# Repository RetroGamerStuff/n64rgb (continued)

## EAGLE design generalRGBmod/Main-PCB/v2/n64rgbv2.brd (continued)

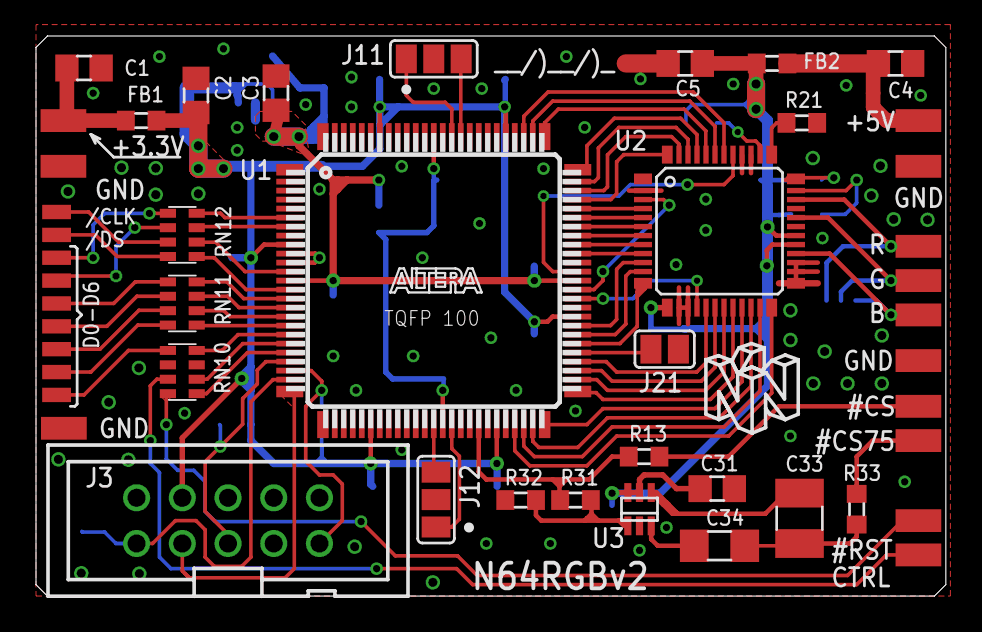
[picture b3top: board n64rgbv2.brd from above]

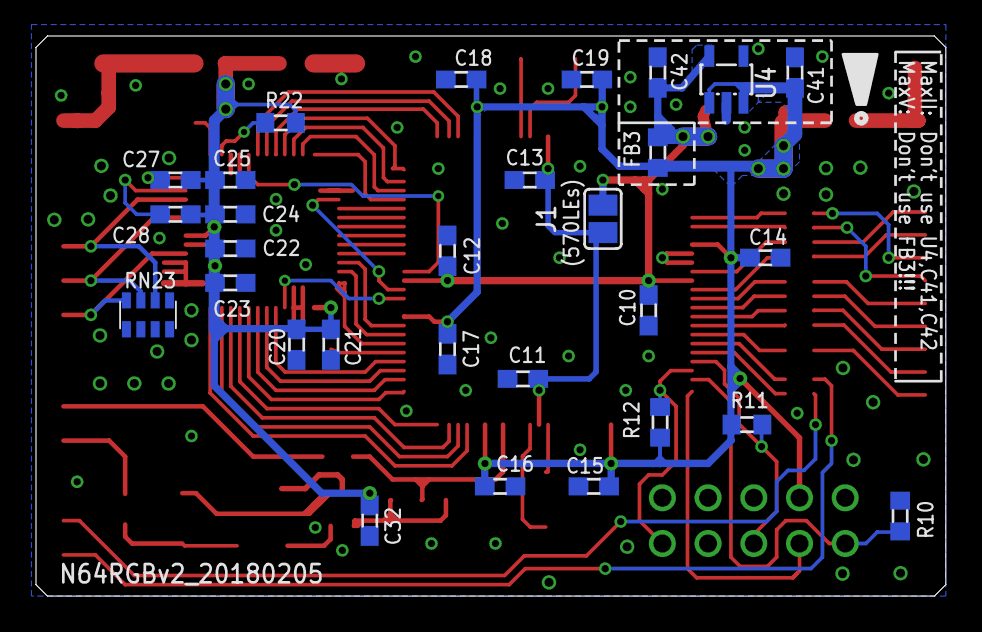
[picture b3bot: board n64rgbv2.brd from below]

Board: 2 copper layers, 50.5 x 31.1 mm, 76 parts (29 on the bottom side), 79 nets.

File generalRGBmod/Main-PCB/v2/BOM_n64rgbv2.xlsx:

Designator | MPN | QTY | DESCRIPTION | VALUE | PACKAGE | NOTES
ICs and Regulators
U1 | 5M570ZT100C4N | 1 | CPLD with 570LEs |  | TQFP100 | Close J1
 | 5M240ZT100C4N |  | CPLD with 240LEs |  | TQFP100 | Alternative to 5M570ZT100 with less LEs, leave J1 open
U2 | ADV7125KSTZ50 | 1 | Video DAC 8bit, 3Ch. |  | 48-LQFP | can be replaced with ADV7123KSTZ50 on demand
U3 | TSH122ICT | 1 | Video buffer |  | SC-70-6
U4 | TLV70018DDCR | 1 | 1.8V LDO regulator |  | SOT-23-5
Power Supply Filtering
C1,C4 | GRM31CR61A476ME15L | 2 | Ceramic capacitor, X5R | 47uF / 6.3V | SMD0805
FB1,FB2 | BLM18PG471SN1D | 2 | Ferrit bead |  | SMD0603
Remaining passive components
C2,C3,C5,C31 | GRM219R60J476ME44D | 4 | Ceramic capacitor, X5R | 10uF / 6.3V | SMD0805
C10-C19,C20,C22,C24,C27,C28 | GRM188R71H104KA93J | 15 | Ceramic capacitor, X7R | 0.1uF / 50V (10%) | SMD0603
C21,C23,C25,C32 | GRM188R70J103KA01D | 4 | Ceramic capacitor, X7R | 0.01uF / 50V | SMD0603
C33 | GRM32DR60J336ME19L | 1 | Ceramic capacitor, X5R | 33uF / 6.3V | SMD1210
C34 | GRM31CR60J226KE19L | 1 | Ceramic capacitor, X5R | 22uF / 6.3V | SMD1206
C41,C42 | GRM18R60J105KA01J | 2 | Ceramic capacitor, X5R | 1uF / 6.3V | SMD0603
R10 | CRCW06031K00FKTB | 1 | Resistor | 1kohm (1%) | SMD0603
R11, R12 | CRCW0603-10K | 2 | Resistor | 10kohm (1%) | SMD0603
R13 | RC0603FR-07330RL | 1 | Resistor | 330ohm (1%) | SMD0603
R21 | RC0603FR-07523RL | 1 | Resistor | 518 | SMD0603 | with ADV7123: use 516ohm resistor; for PAL-Standard: 528ohm/527ohm
R22,R31 | RC0603FR-074K7L | 2 | Resistor | 4.7kohm (1%) | SMD0603
R32 | RC0603FR-07475RL | 1 | Resistor | 475ohm (1%) | SMD0603
R33 | RC0603FR-0775RL | 1 | Resistor | 75 | SMD0603
RN10,RN11,RN12 | CAT16-47R0F4LF / CAY16-47R0F4LF | 3 | Resistor Array (4x) | 47 | SMD1206 | Only use this if you don't have resistors at the RCP output
 | BK32164M121-T |  | Ferrite Beads MULTILYR CHP | BD 120OHMS 25% | SMD1206 | Use this if you have resistors at the RCP output
RN23 | CAT16-75R0F4LF / CAY16-75R0F4LF | 1 | Resistor Array (4x) | 75 | SMD1206
J3 | 30310-6002HB | 1 |  |  |  | JTAG Connector
Unpopulated Footprints
FB3 | Don't use FB3 in MaxV setup!!! Otherwise you'll harm your CPLD at first power c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
MPNs are only suggestions! You can use equivalent components, too.

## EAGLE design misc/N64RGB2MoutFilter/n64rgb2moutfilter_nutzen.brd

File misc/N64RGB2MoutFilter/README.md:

### Jumper

#### SJ1

Sync source at MultiOut
 - SJ1.1 closed: forward sync to pin 7 of the MultiOut
 - SJ1.2 closed: forward sync to pin 3 of the MultiOut
 - you are allowed to close both sides of this jumper

#### SJ2

flex assembly setup (see [BOM sheet](./doc/N64RGB2MoutFilter_BOM.xlsx)
 - close all three jumper if you do not use the filter assembly

#### SJ3

Sync source at the modding board
 - J3.1: Use TTL C-Sync
 - J3.2: Use 75ohm Sync
 - Never use both!

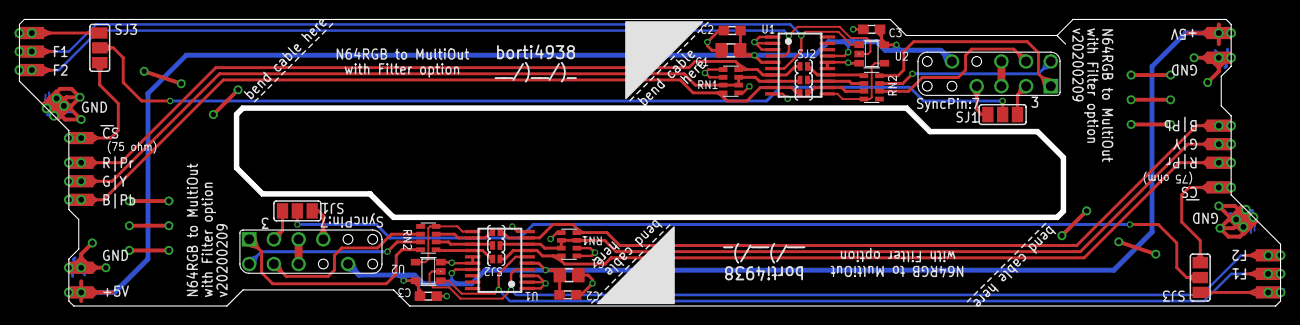
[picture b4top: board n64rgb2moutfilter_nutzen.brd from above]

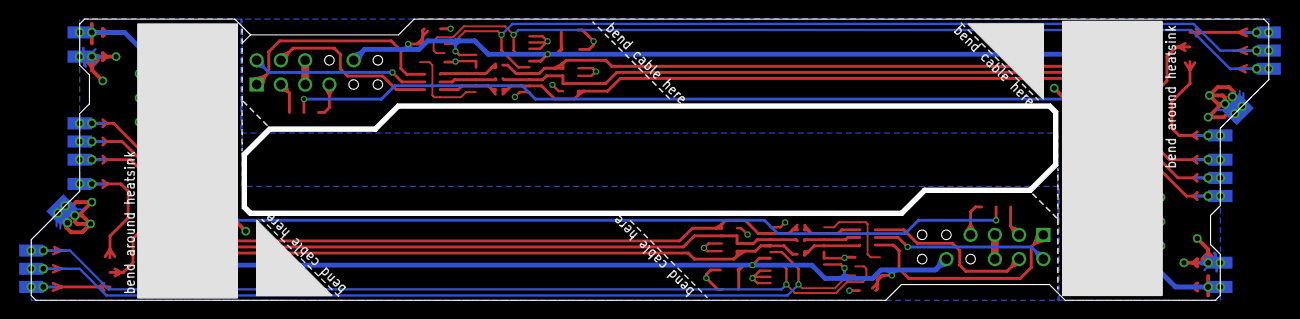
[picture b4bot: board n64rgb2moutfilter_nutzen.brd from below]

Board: 2 copper layers, 129.7 x 29.5 mm, 70 parts (22 on the bottom side), 38 nets.

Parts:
B/PB, B/PB1, B/PB2, B/PB3: SMD1,27-2,54
C1, C4: 22u; C0805
C2, C3, C5, C6: 0.1u; C0603
CS75#, CS75#1, CS75#2, CS75#3: SMD1,27-2,54
CS#, CS#1, CS#2, CS#3: SMD1,27-2,54
E$1, E$2: SNES_MULTIAV_RGBSY
F1, F2, F3, F4, F5, F6, F7, F8: SMD1,27-2,54
G/Y, G/Y1, G/Y2, G/Y3: SMD1,27-2,54
P_GND1, P_GND2, P_GND3, P_GND4, P_GND5, P_GND6, P_GND7, P_GND8, P_GND9, P_GND10, P_GND11, P_GND12: SMD1,27-2,54
P_VCC_5V, P_VCC_5V1, P_VCC_5V2, P_VCC_5V3: SMD1,27-2,54
R/PR, R/PR1, R/PR2, R/PR3: SMD1,27-2,54
RN1, RN2, RN3, RN4: 75; CTS742C083
SJ1, SJ2, SJ3, SJ4: SJ_2
SJ2B, SJ2B1, SJ2G, SJ2G1, SJ2R, SJ2R1: SJ_SMALL
U1, U3: THS7368
U2, U4: SOT23-5

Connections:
5V: C1.2, C2.1, C3.1, E$1.10, P_VCC_5V.1, P_VCC_5V1.1, U1.5, U1.17, U2.5
5V1: C4.2, C5.1, C6.1, E$2.10, P_VCC_5V2.1, P_VCC_5V3.1, U3.5, U3.17, U4.5
#CS: E$1.3, SJ1.1
#CS1: E$2.3, SJ2.1
#CS.75.I: CS75#.1, CS75#1.1, SJ3.3
#CS.75.I1: CS75#2.1, CS75#3.1, SJ4.3
#CS.I: CS#.1, CS#1.1, SJ3.1
#CS.I1: CS#2.1, CS#3.1, SJ4.1
#CS.SEL: SJ1.2, SJ3.2
#CS.SEL1: SJ2.2, SJ4.2
BLUE: B/PB.1, B/PB1.1, RN1.8, SJ2R.1, U1.9
BLUE1: B/PB2.1, B/PB3.1, RN3.8, SJ2R1.1, U3.9
BLUE.OUT: RN2.3, SJ2R.2, U1.12
BLUE.OUT1: RN4.3, SJ2R1.2, U3.12
BLUE.OUT.1: E$2.4, RN4.6
BLUE.OUT.75: E$1.4, RN2.6
BYPASS_SF: RN2.4, U1.11, U2.4
BYPASS_SF1: RN4.4, U3.11, U4.4
F1: F1.1, F4.1, U1.6, U2.1
F2: F2.1, F3.1, U1.4, U2.2
F3: F5.1, F8.1, U3.6, U4.1
F4: F6.1, F7.1, U3.4, U4.2
GND: C1.1, C2.2, C3.2, E$1.5, E$1.6, P_GND1.1, P_GND2.1, P_GND3.1, P_GND4.1, P_GND5.1, P_GND6.1, RN1.1, RN1.5, RN1.6, U1.1, U1.2, U1.3, U1.10, U1.15, U1.16, U2.3
GND1: C4.1, C5.2, C6.2, E$2.5, E$2.6, P_GND7.1, P_GND8.1, P_GND9.1, P_GND10.1, P_GND11.1, P_GND12.1, RN3.1, RN3.5, RN3.6, U3.1, U3.2, U3.3, U3.10, U3.15, U3.16, U4.3
GREEN: G/Y.1, G/Y1.1, RN1.2, RN1.3, RN1.7, SJ2G.1, U1.8
GREEN1: G/Y2.1, G/Y3.1, RN3.2, RN3.3, RN3.7, SJ2G1.1, U3.8
GREEN.OUT: RN2.2, SJ2G.2, U1.13
GREEN.OUT1: RN4.2, SJ2G1.2, U3.13
GREEN.OUT.1: E$2.2, RN4.7
GREEN.OUT.75: E$1.2, RN2.7
LUMA: E$1.7, SJ1.3
LUMA1: E$2.7, SJ2.3
RED: R/PR.1, R/PR1.1, RN1.4, SJ2B.1, U1.7
RED1: R/PR2.1, R/PR3.1, RN3.4, SJ2B1.1, U3.7
RED1.OUT: RN2.1, SJ2B.2, U1.14
RED1.OUT1: RN4.1, SJ2B1.2, U3.14
RED.OUT.1: E$2.1, RN4.8
RED.OUT.75: E$1.1, RN2.8

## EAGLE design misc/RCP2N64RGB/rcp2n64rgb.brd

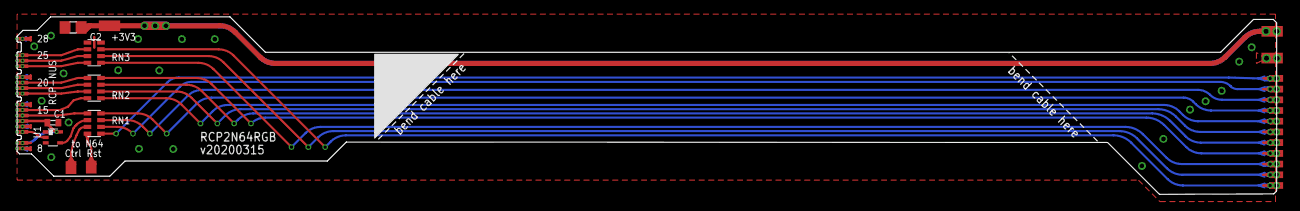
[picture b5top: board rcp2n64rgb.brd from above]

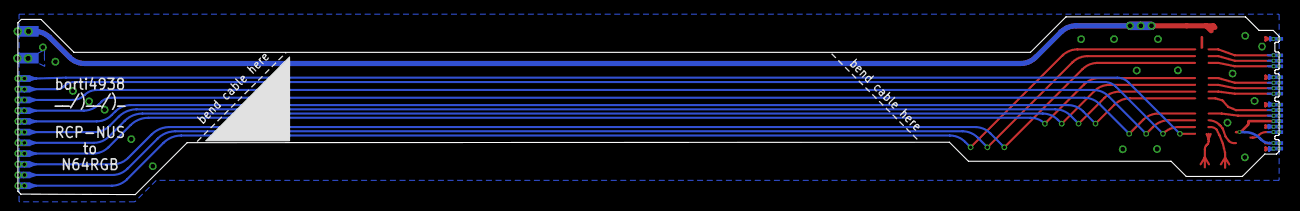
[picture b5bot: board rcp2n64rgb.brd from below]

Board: 2 copper layers, 149.4 x 21.1 mm, 67 parts (29 on the bottom side), 26 nets.

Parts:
/RST_A, /RST_A1: SMD0,8-1,6
C1: C0402
C2: 22u; C0805
CLOCK#, CLOCK#1: SMD0,8-1,6
CTRL_A, CTRL_A1: SMD0,8-1,6
D0, D1, D2, D3, D4, D5, D6, D7, D8, D9, D10, D11, D12, D13: SMD0,8-1,6
DSYNC#, DSYNC#1: SMD0,8-1,6
E$1, E$3, E$4, E$5, E$8, E$9, E$10, E$11, E$12, E$13, E$14, E$15, E$16, E$17, E$18, E$19, E$22, E$23, E$24, E$25, E$26, E$27, E$28, E$29, E$30, E$31, E$32, E$33, E$43, E$46, E$47: SMD0,45-1,35
E$2, E$6: SMD0.8SQ
GND: SMD0,45-1,35
P_GND0, P_GND1: SMD1,27-2,54
P_VCC_3V, P_VCC_3V1, P_VCC_3V3: SMD1,27-2,54
RN1, RN2, RN3: CTS742C083
U1: DCK_R-PDSO-G5

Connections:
3V3: C2.1, P_VCC_3V.1, P_VCC_3V1.1, P_VCC_3V3.1
#DSYNC: E$10.P$1, E$31.P$1, RN1.1
#DSYNC.1: DSYNC#.P$1, DSYNC#1.P$1, RN1.8
CTRL: E$2.P$1, RN1.3
CTRL.1: CTRL_A.P$1, CTRL_A1.P$1, RN1.6
D0: E$19.P$1, E$22.P$1, RN3.2
D0.1: D0.P$1, D7.P$1, RN3.7
D1: E$18.P$1, E$23.P$1, RN3.3
D1.1: D1.P$1, D8.P$1, RN3.6
D2: E$17.P$1, E$24.P$1, RN3.4
D2.1: D2.P$1, D9.P$1, RN3.5
D3: E$15.P$1, E$26.P$1, RN2.1
D3.1: D3.P$1, D10.P$1, RN2.8
D4: E$14.P$1, E$27.P$1, RN2.2
D4.1: D4.P$1, D11.P$1, RN2.7
D5: E$13.P$1, E$28.P$1, RN2.3
D5.1: D5.P$1, D12.P$1, RN2.6
D6: E$11.P$1, E$30.P$1, RN2.4
D6.1: D6.P$1, D13.P$1, RN2.5
GND: C1.2, C2.2, E$9.P$1, E$12.P$1, E$16.P$1, E$25.P$1, E$29.P$1, E$32.P$1, E$43.P$1, E$46.P$1, GND.P$1, P_GND0.1, P_GND1.1, RN3.1, RN3.8, U1.3
RST: E$6.P$1, RN1.4
RST.1: /RST_A.P$1, /RST_A1.P$1, RN1.5
VCC: C1.1, E$1.P$1, E$3.P$1, E$4.P$1, E$5.P$1, U1.5
VCLK: E$8.P$1, E$33.P$1, U1.2
VCLK.1: CLOCK#.P$1, CLOCK#1.P$1, RN1.7
VCLK_BUF: RN1.2, U1.4

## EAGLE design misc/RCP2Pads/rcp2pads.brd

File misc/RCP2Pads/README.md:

# A small Flex-PCB
## N64 RCP-NUS breakout

## Purpose

This PCB enables you to apply appropriate buffering to the RCP output pins for N64RGB installs. This is useful for any CPLD and FPGA RGB Kit like viletims N64RGB (public and commercial), N64RGBv2.1, N64Advanced and many more variations spreaded over the internet.

## Where to Order?

This board can be ordered from every service you want to choose, e.g. PCBWay.  
An easy small prototype solution though might be the flex cable service by [OSHPark](https://oshpark.com/).
Make sure to tick the flex service before going to the checkout when chosing for OSHPark!

## Pinout

From top to bottom (RCP on left, connector right)

| **Pin** | **Signal** |
|:-------:|:-----------|
| 13 | GND |
| 12 | D0 |
| 11 | D1 |
| 10 | D2 |
| 9 | D3 |
| 8 | D4 |
| 7 | D5 |
| 6 | D6 |
| 5 | #DSYNC |
| 4 | VCLK |
| 3 | GND |
| 2 | Ctrl. (controller port pin 2, pin 16 PIF-NUS) |
| 1 | Rst (pin 27 PIF-NUS) |

## Preparation

You need components as listed in BOM.
Assemble the board.
The ferrite bead / resistor arrays don't have an orientation.

## Installation

Solder the FPC board to the output pins 8 - 28 (pin 5 has a dot, pin 30 also) of the RCP-NUS.

Connect pad for Ctrl. and Rst. as stated in the table above. More information about appropriate solder points can be found in the Guide.

Use the pads to connect your modding kit. Note the pinout of the modding kit. If possible, keep/run VCLK separated from data wires.

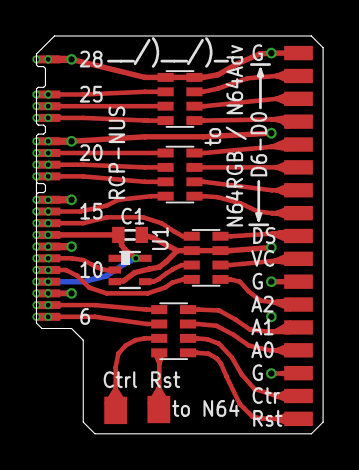
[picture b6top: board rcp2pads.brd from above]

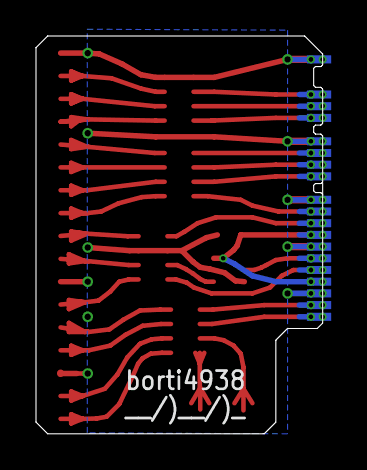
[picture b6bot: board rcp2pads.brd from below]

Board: 2 copper layers, 15.9 x 22.1 mm, 63 parts (19 on the bottom side), 31 nets.

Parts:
C1: C0402
E$2, E$6: SMD0.8SQ
E$7, E$8, E$9, E$10, E$11, E$12, E$13, E$14, E$15, E$16, E$17, E$18, E$19, E$22, E$23, E$24, E$25, E$26, E$27, E$28, E$29, E$30, E$31, E$32, E$33, E$34, E$35, E$37, E$38, E$40, E$41, E$43, E$44, E$45, E$46, E$47: SMD0,45-1,35
E$20, E$21, E$36, E$39, E$48, E$49, E$50, E$51, E$53, E$54, E$55, E$56, E$57, E$58, E$59, E$60, E$61: SMD0,8-1,6
GND: SMD0,45-1,35
LRCLK: SMD0,45-1,35
RN1, RN2, RN3, RN4: CAY16-330J4LF; CTS742C083
U1: SN74LVC1G17DCKR; DCK_R-PDSO-G5

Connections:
#DSYNC: E$10.P$1, E$31.P$1, RN3.1
#DSYNC.1: E$53.1, RN3.8
CTRL: E$2.P$1, RN4.7
CTRL.1: E$60.1, RN4.2
D0: E$19.P$1, E$22.P$1, RN1.2
D0.1: E$20.1, RN1.7
D1: E$18.P$1, E$23.P$1, RN1.3
D1.1: E$36.1, RN1.6
D2: E$17.P$1, E$24.P$1, RN1.4
D2.1: E$39.1, RN1.5
D3: E$15.P$1, E$26.P$1, RN2.1
D3.1: E$48.1, RN2.8
D4: E$14.P$1, E$27.P$1, RN2.2
D4.1: E$49.1, RN2.7
D5: E$13.P$1, E$28.P$1, RN2.3
D5.1: E$50.1, RN2.6
D6: E$11.P$1, E$30.P$1, RN2.4
D6.1: E$51.1, RN2.5
GND: C1.2, E$9.P$1, E$12.P$1, E$16.P$1, E$21.1, E$25.P$1, E$29.P$1, E$32.P$1, E$43.P$1, E$46.P$1, E$55.1, E$59.1, GND.P$1, RN1.1, RN1.8, RN3.2, RN3.7, U1.3
LRCLK: E$38.P$1, RN3.4
LRCLK.1: E$56.1, RN3.5
RST: E$6.P$1, RN4.8
RST.1: E$61.1, RN4.1
SCLK: E$41.P$1, RN4.6
SCLK.1: E$58.1, RN4.3
SDATA: E$40.P$1, RN4.5
SDATA.1: E$57.1, RN4.4
VCC: C1.1, E$7.P$1, E$34.P$1, E$35.P$1, E$37.P$1, U1.5
VCLK: E$8.P$1, E$33.P$1, U1.2
VCLK.1: E$54.1, RN3.6
VCLK_BUF: RN3.3, U1.4

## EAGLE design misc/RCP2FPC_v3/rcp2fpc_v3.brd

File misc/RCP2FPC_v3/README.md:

# A small Flex-PCB
## N64 RCP-NUS -> to 24pin 0.5mm pitch FPC cable connector

## Purpose

This PCB enables you to connect your N64Advanced Version 2 (HDMI) modding kit with a FPC cable.

## Pinout of version 3

From top to bottom (RCP on left, connector right)

| **Pin** | **Signal** |
|:-------:|:-----------|
| 24 | 3.3V |
| 23 | 3.3V |
| 22 | 3.3V |
| 21 | GND |
| 20 | GND |
| 19 | D0 |
| 18 | D1 |
| 17 | D2 |
| 16 | D3 |
| 15 | D4 |
| 14 | D5 |
| 13 | D6 |
| 12 | GND |
| 11 | #DSYNC |
| 10 | GND |
| 9 | VCLK |
| 8 | GND |
| 7 | LRCLK (Audio) |
| 6 | SDATA (Audio) |
| 5 | GND |
| 4 | SCLK (Audio) |
| 3 | GND |
| 2 | Ctrl. (controller port pin 2, pin 16 PIF-NUS) |
| 1 | Rst (pin 27 PIF-NUS) |

## Preparation

You need

- four resistor arrays: 4x47ohm parallel, SMD1206, e.g. CAT16-47R0F4LF or CAY16-47R0F4LF
- one FPC cable connector: 24 pin, 0.5mm pitch

Assemble the board. The resistor arrays don't have an orientation, the connector should be clear.
Make sure that you don't have a short at the connector.

## Installation

Solder the FPC board to the output pins 6 - 28 (pin 5 has a dot, pin 30 also) of the RCP-NUS.

Connect pad for Ctrl. and Rst. as stated in the table above. More information about appropriate solder points can be found in the Guide.

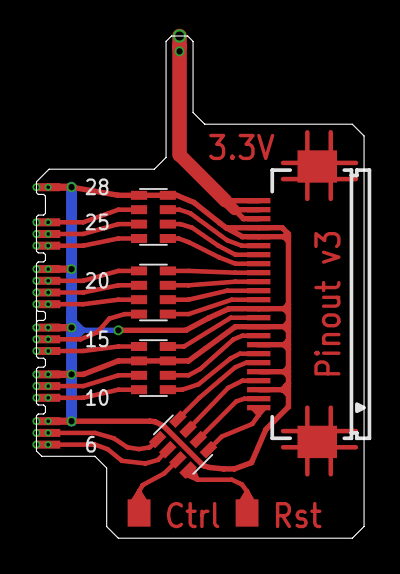
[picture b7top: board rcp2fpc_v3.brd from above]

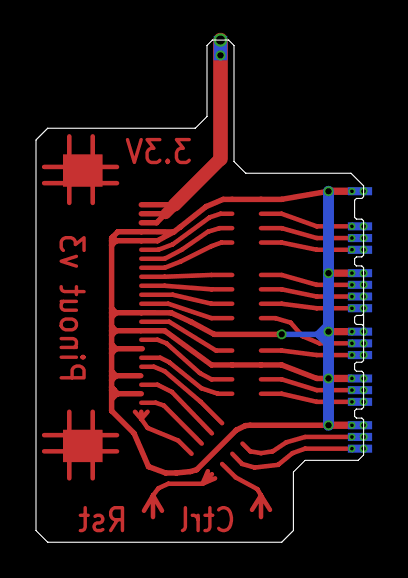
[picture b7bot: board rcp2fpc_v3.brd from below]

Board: 2 copper layers, 18.2 x 27.9 mm, 44 parts (19 on the bottom side), 30 nets.

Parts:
E$1, E$3, E$4, E$5: CTS742C083
E$2, E$6: SMD0.8SQ
E$7: FH12-24S-0.5SH
E$8, E$9, E$10, E$11, E$12, E$13, E$14, E$15, E$16, E$17, E$18, E$19, E$22, E$23, E$24, E$25, E$26, E$27, E$28, E$29, E$30, E$31, E$32, E$33, E$34, E$35, E$37, E$38, E$40, E$41, E$42, E$43, E$44, E$45, E$46, E$47: SMD0,45-1,35
GND: SMD0,45-1,35

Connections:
3V3: E$7.22, E$7.23, E$7.24, E$34.P$1, E$35.P$1
#DSYNC: E$5.1, E$10.P$1, E$31.P$1
#DSYNC.1: E$5.8, E$7.11
CTRL: E$1.7, E$2.P$1
CTRL.1: E$1.2, E$7.2
D0: E$3.2, E$19.P$1, E$22.P$1
D0.1: E$3.7, E$7.19
D1: E$3.3, E$18.P$1, E$23.P$1
D1.1: E$3.6, E$7.18
D2: E$3.4, E$17.P$1, E$24.P$1
D2.1: E$3.5, E$7.17
D3: E$4.1, E$15.P$1, E$26.P$1
D3.1: E$4.8, E$7.16
D4: E$4.2, E$14.P$1, E$27.P$1
D4.1: E$4.7, E$7.15
D5: E$4.3, E$13.P$1, E$28.P$1
D5.1: E$4.6, E$7.14
D6: E$4.4, E$11.P$1, E$30.P$1
D6.1: E$4.5, E$7.13
GND: E$3.1, E$3.8, E$5.2, E$5.7, E$7.3, E$7.5, E$7.8, E$7.10, E$7.12, E$7.20, E$7.21, E$9.P$1, E$12.P$1, E$16.P$1, E$25.P$1, E$29.P$1, E$32.P$1, E$46.P$1
LRCLK: E$5.4, E$38.P$1
LRCLK.1: E$5.5, E$7.7
RST: E$1.8, E$6.P$1
RST.1: E$1.1, E$7.1
SCLK: E$1.6, E$41.P$1
SCLK.1: E$1.3, E$7.4
SDATA: E$1.5, E$40.P$1
SDATA.1: E$1.4, E$7.6
VCLK: E$5.3, E$8.P$1, E$33.P$1
VCLK.1: E$5.6, E$7.9

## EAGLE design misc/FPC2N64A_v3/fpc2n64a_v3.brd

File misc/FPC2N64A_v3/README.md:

# A PCB adapter
## FPC cable connector to N64Advanced

## Purpose

This PCB enables you to connect your N64Advanced modding kit with a FPC cable.

## Pinout of version 3

From top to bottom (N64A main on right)

| **Pin** | **Signal** |
|:-------:|:-----------|
| 24 | Rst |
| 23 | Ctrl. |
| 22 | GND |
| 21 | n.c. |
| 20 | GND |
| 19 | n.c. |
| 18 | n.c. |
| 17 | GND |
| 16 | VCLK |
| 15 | GND |
| 14 | #DSYNC |
| 13 | GND |
| 12 | D6 |
| 11 | D5 |
| 10 | D4 |
| 9 | D3 |
| 8 | D2 |
| 7 | D1 |
| 6 | D0 |
| 5 | GND |
| 4 | GND |
| 3 | 3.3V |
| 2 | 3.3V |
| 1 | 3.3V |

## Preparation

You need

- one FPC cable connector: 24 pin, 0.5mm pitch
- one FPC cable 24pin with 0.5mm pitch of length 15cm with connectors on same side 

Assemble the board; orientation of the connector should be clear.
Make sure that you don't have a short at the connector.

## Installation

Solder the adapter board to the data inputs of the N64A modding board.
You only have small vias available. So make sure 
 
- to allign the board prior to set the first solder joint
- to make good solder joints (the solder has to flow through the connection vias down to the pads)

Connect the pads for the Controller and Reset to the pads at the pads on the modding board. You can also make a short connection to the neighbored resistor array (pin 1 and 3 of RN12).

Finally, connect the modding board to the installed RCP2FPC_v3 board.

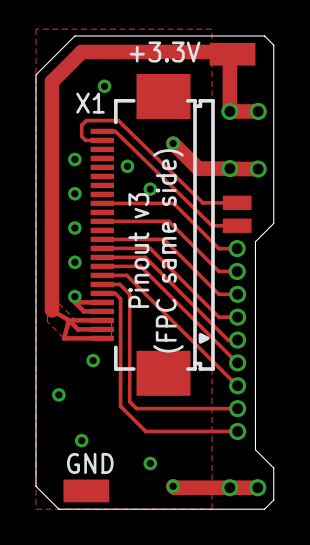
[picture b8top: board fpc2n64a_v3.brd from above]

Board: 2 copper layers, 13.2 x 26.3 mm, 5 parts (0 on the bottom side), 4 nets.

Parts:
/RST: SMD0,8-1,6
CTRL: SMD0,8-1,6
GND: SMD1,27-2,54
VCC: SMD1,27-2,54
X1: FH12-24S-0.5SH

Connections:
3V3: VCC.1, X1.1, X1.2, X1.3
#RST: /RST.P$1, X1.24
CTRL: CTRL.P$1, X1.23
GND: GND.1, X1.4, X1.5, X1.13, X1.15, X1.17, X1.20, X1.22

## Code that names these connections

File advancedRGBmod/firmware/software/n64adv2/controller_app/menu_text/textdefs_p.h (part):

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const char *LinkSL[]        = {"480i ind.","Link 240p"};
const char *VideoMode[]     = {"240p60","480i60","288p50","576i50","480p60","576p50"};
const char *VideoColor[]    = {"21bit","15bit"};
const char *VideoFormat[]   = {"RGBS","RGBS/RGsB","YPbPr"};
const char *DeBlur[]        = {"(estimated)","(forced)","(480i/576i)"};
const char *DeBlurCfg[]     = {"Auto","Off","Always"};
const char *SLDesc[]        = {"  0.00%","  6.25%"," 12.50%"," 18.75%",
                               " 25.00%"," 31.25%"," 37.50%"," 43.75%",
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                               "150.00%"};

const char *GammaValue[]    = {"0.75","0.80","0.85","0.90","0.95","1.00","1.05","1.10","1.15"};
const char *QuickChange[]   = {"Off","DeBlur","15bit mode","All"};

#endif /* MENU_TEXT_TEXTDEFS_P_H_ */

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
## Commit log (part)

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2018-02-08 yet another bugfix (incl. builds)
2018-02-08 a lot of refactoring stuff: - register some logic - remove some redundant registers - improve 480i/576i detection - commit includes fw-builds
2018-02-09 reviewing some deblur stuff (stability of estimation, especially on CPLD versions)
2018-02-09 VI-Deblur bugfix
2018-02-09 some more VI-Deblur and register replacement stuff
2018-02-16 update configuration structure: - organized in 4x 8bit words - some bits reserved for future use
2018-02-16 use flash functions only if first check haven't failed
2018-02-17 minor bugfixes
2018-02-17 small bugfix (trend were decreased while estimation was not running)
2018-02-18 osd params corrected
2018-02-18 misc updates: - increase compared number of bits for deblur estimation - small bug fix (trend was decreased if estimation were not running) - minimize area during synthesis to get a closer match to f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
2018-02-18 provide (hopefully) stable programming files
2018-02-18 programming files for latest changes
2018-02-19 do not execute load/save from/to flash if not initialized
2018-02-19 remove obsolete leavetype
2018-02-19 add some comments
2018-02-20 some small bugfixes
2018-02-21 - Test-Update: latch input data on rising edge instead of falling edge - optimize hold timing on all paths (which seems to have no effect on the CPLD versions) - remove two falsely set synthesis and 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
2018-02-22 add timing constraints and remove synthesis assignment to met timing analysis
2018-02-22 re-introduce half pixel shift removing between deblur on and off
2018-02-22 move osd menu to the rigth for PAL mode
2018-02-22 small text adaptation
2018-03-08 add smart recompile to qsf
2018-03-08 add setup and hold time from ADV7125 to timing constraints
2018-03-08 add programming files and update project files
2018-03-09 new programming files, update project files and small quick bugfix in advanced project
2018-03-17 option for hybrid scanlines
2018-03-17 small text update
2018-03-18 add "don't use scanlines in OSD menu" as an option
2018-03-25 logo implementation
2018-03-25 small font adaptation
2018-03-26 rename function apply_command to modify_menu
2018-03-27 firmware builds for recent commits
2018-04-05 Confirm load/save and minor improvements
2018-04-15 discontinue 6k LE FPGA support for now
2018-04-22 add menu to guide
2018-05-01 third party controller support (e.g. Hori pad)
2018-05-09 bump to Quartus Prime 18.0
2018-05-10 Update BOM - fix some broken links (Mouser) of ICs - Replace U5 - Passive components untouched
2018-05-11 replace vdemux
2018-05-11 support ram pages
2018-05-11 bump also n64rgb to QP 18.0
2018-05-11 update programming and project files (incl. header in n64a top module) after recent commits
2018-05-26 info and warning window template
2018-05-26 add some pics
2018-05-27 remove unnecessarily committed file
2018-05-31 initial commit (RCP-NUS break out; untested)
2018-06-17 initial commit (RCP-NUS break out)
2018-06-22 Revert "refine linebuf.v to not rely on synthesis optimization"
    This reverts commit 3f9c6e86b52bf000c7d36ee04d0fb0e85d229fc9.
    Implementation was buggy - I'm sorry for any inconvenience caused
2018-07-20 remove vclk-pll for stability consernings in certain circumstances
2018-07-25 update PCB - add fields for GND shield fingers and remove pad for /COLD
2018-07-25 remove designs which are in experimental stage
2018-07-26 synchronize reset for video related blocks
2018-07-26 update programming files and fw-number
2018-08-14 add missing false path
2018-08-15 implementation of advanced scanline drawing technique This technique takes the previous line (even scanline) or the next (odd scanline) into account for calculation and drawing the scanline. This smo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
2018-08-16 parameterize number of buffer pages
2018-08-16 increase buffer size to five lines (by the costs of memory space for NIOS II soft core)
2018-08-16 stabilize 480i-linex2 output (reduce/no vertical twitching)
2018-08-16 scanlines in 480i linex2 mode allowed (no advanced scanlines)
2018-08-17 remove outdated comment
2018-08-17 update firmware number (equalization of subversion number of hard- and software code)
2018-08-20 increase buffer size (just because it fits)
2018-08-21 remove revision numbering in headers
2018-08-21 move gamma correction into a dedicated module (incl. update remaining header)
2018-08-21 increase false_path list
2018-08-21 update programming and project files for recent bug fixes
2018-08-22 correct reset values in rgb2ypbpr converter
2018-09-04 remove needless lines
2018-09-04 parameterize testpattern (alpha)
2018-09-13 file adaptations for new folder structure
2018-09-14 update project files for recent commits
2018-09-14 FPC adapter
2018-09-14 remove outdated file
2018-09-14 init commit of N64Adv2 firmware (not functional yet)
2018-09-14 update gitignore
2018-09-29 modify outline layer a bit
2018-09-29 bump to quartus prime 18.1
2018-10-11 bump to QP v18.1
2018-10-11 minor cosmetic changes
2018-10-11 add mising files and changes
2018-10-19 enable clock div mux output
2018-10-19 prepare separate scaler / linedoubler unit for N64Aadv1 and N64Adv2
2018-10-19 480p as default
2018-10-22 update on APU module: audio is now working
2018-10-30 remove header from constraint files
2018-10-30 alternating constraint on output paths hopefully removing color quirk
2018-11-04 correct and remove some remainings
2018-11-04 move DE gen into ADV and outline 240p support
2018-11-04 remove useless ports
2018-11-05 move sync generation to reading process, remove a useless port and tiny bugfix (glitchy linex2 in 480i due to tight timing)
2018-11-05 update project and firmware files
2018-11-06 remove useless value from OSDInfo vector
2018-11-06 add testbenches for APU
2018-11-11 remove connections for DE and MCLK and change pinout for system LEDs
2018-12-07 increase via at center of exposed pad for easier DIY soldering
2018-12-25 sync in reset for audio logic
2019-01-25 pcb update: add some additional pads for rst and ctrl io
2019-02-12 remove system clock enable from pinout (rely on weak pull-up)
2019-02-12 linex3 for 240p60 input and some cosmetic changes
2019-03-06 refactoring of timing analysis to improve fitting
2019-03-06 introduce new CPLD for N64RGBv1 and v2 which now meets timings
2019-03-17 refactoring reset logic and sync between asynchronous paths
2019-03-18 formatting stuff
2019-04-11 upload new design for RCP2Pads
2019-10-05 menu und functionality updates: - LineX2 without VPLL - optional VPLL use for LineX3 - Feedback channel from PPU to NIOS II (uC was guessing before)
2019-10-11 bugfix in BOM (thanks to Sefirosu789 and unmaker from shmups forumfor pointing that out!)
2019-10-14 yet another tinz bugfix plus fw. version update
2019-10-15 detecting FilterAddon properly and removing false friends in constant namings
2019-11-27 raw binary for production runs and easier DIY (for those who do not have a USB Blaster)
2020-01-20 update year in copyright notes
2020-01-20 control menu with analog stick
2020-01-20 simplify clock network
2020-01-20 minor update (weak pull up instead of bus hold for unused pins)
2020-01-22 bugfix in configureable deblur algorithm update fw files
2020-01-26 bank separation between digital video in and digital video outs using 2.5V LDO
2020-02-14 fix header quirk in mfiles
2020-02-14 update firmware files
2020-02-18 update firmware
2020-03-18 bugfix: misc menu wasn't working correctly for non-filter addon installs
2020-03-19 update firware files
2020-03-22 update N64Adv board: - csync level selection by jumper - output IO bank powered by 5V rail (over a 3.3V ldo)
2020-03-22 somne new production data for the filter addon board
2020-03-22 coordinate files
2020-03-22 N64RGBv2.1 - inputs and outputs separated at different IO Banks - outputs powered by 5V rail (over a 3.3V LDO) - PCB design allows for usage of flex designs (initially meant for the N64Adv) - PCB mad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
2020-04-05 incremental improvements after first prototype run
2020-07-05 remove firmware for viletims N64RGB from repository
2020-07-05 change duty cycle at pll out to 60% (same as input)
2020-07-08 alter timings a bit incl. adding a safety margin for tsu and th for ADV7125
2020-07-08 ignore controller inputs after opening the menu for a few frames
2020-07-08 update firmware and project files
2020-07-08 update BOM for new flex cable concept
2020-07-09 update and add some documentation
2020-07-12 bugfix: repair url to correct IC @ U7
2020-07-13 remove unneccessary registers
2020-07-13 new firmware files and new naming to make clear that firmware is for v2.1
2020-07-15 formatting
2020-07-15 remove magic numbers
2020-07-15 update fw no., project files and firmware files
2020-08-18 bug fixes and incremental improvements in gamma2rom.m script
2020-08-18 passing video data sync through all modules
2020-08-18 multicycle analysis - somehow tedious - might be simpler using something like 'set enabled_regs [get_fanouts [get_pins enable_reg|q] –through [get_pins –hierarchical *|ena]]'
2020-08-19 typo fix
2020-08-19 rework with sdc
2020-09-17 remove auto deblur stuff from N64RGB - I found more and more situations where the auto detection does not work reliable - so I removed it for now
2020-09-18 add THS7374 rgb amp by TzorriMahm as submodulee
2020-09-18 misc updates: - remove deblur heuristic function (same reason as for the N64RGBv2.1) - undo commits 7cbfe9ac1eb809ba2aa9ed5b957db946c618042d, ba99bacb24be1f8a60ceded04c9939a554467d6a, 1f774a66b1c449c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
2020-09-19 update input timings
2020-09-19 do not run JTAG through other pins as this may cause problem if used CPLDs are assembled
2020-09-19 update fw for older PCB versions (removing deblur heuristics)
    (cherry picked from commit 10f550d924fbe1fe2ecd3e1af62ef39604ccbc32)
2020-09-19 update BOM
    (cherry picked from commit c3bb21dca278fcc9a3faaef770ff45191a9fccf5)
2020-09-21 Update jumper and menu description
2020-11-28 fix unnecessary sign error in sdc
2020-11-28 bump to Quartus Prime Lite 20.1
2020-11-29 change vi-config pages a bit
2020-12-06 tiny fix: put not variable declaration in while(1) loop
2020-12-06 revise some numbers
2020-12-08 use valid data flag in order to account for 4x pixelclock
2020-12-12 register shift correction at output
2020-12-12 put wire and reg defs to top of file
2020-12-20 move gamma table offset definition from vparams to ppuconfig
2020-12-20 move OSD a bit to middle of the screen especially for PAL content (menu was at very left of the screen)
2020-12-27 tiny text adaptation
2020-12-27 tiny fix at preset value width
2020-12-31 16bit mode instead of 15bit (one bit more for green)
2021-01-04 name adaptations
2021-01-04 minor bug fix (nVDSYNC not part of sensitivity list)
2021-01-04 add default state to state machine
2021-01-04 remove outdated files
2021-01-05 tiny adaptations: - remove outdated lines - text fixes
2021-01-05 PPU update: - horizontal shift for passthrough mode (still needs work) - place testpattern infront of gamma module in order to use linex modes afterwards
2021-01-06 update firmware version
2021-01-06 update documentation (still an annoying task)
2021-01-07 firmware files for older v1 and v2 PCBs
    (cherry picked from commit f7c00406ce4fe6c302de748c701290437dd5368d)
2021-01-07 add changelog file for N64Adv firmware
2021-01-15 tiny tiny fixes
2021-01-15 buggfix: HV Sync was not working
2021-01-23 bug fix (impulse width counter was not resetted correctly, which reduced tolerance by half)
2021-01-26 move sysconfig to config.c/.h
2021-02-01 remove register, which is not used
2021-02-01 review implementation of osd_injection module
    (cherry picked from commit 01b561090bf988785a58571093a572e002666fe1)
2021-02-01 remove "begin ... end" (as not needed)
    (cherry picked from commit 36cb327da6bd7ef0298311bb64a74395c50c0816)
2021-02-02 fix some formatting issues
2021-02-07 update flash init and remove old commented lines
2021-03-26 update changelog
2021-03-26 show PPU feedback value in menu (might be useful for better support)
2021-03-26 fix nVSYNC detection for 4MHz clock
2021-03-26 fix video valid window
2021-03-26 tiny sdc fix
2021-04-08 some more documentation tweaks
